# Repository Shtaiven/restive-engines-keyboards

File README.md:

# restive.engines Keyboards

## Introduction

This repository contains design and manufacturing files created by Steven Eisinger (@Shtaiven a.k.a. restive.engines). Everything you need to manufacture one of my keyboards can be found here, including pcbs, cases, and certain keycaps.

For keyboard firmware, please refer to my [ZMK config repo](https://github.com/Shtaiven/restive-engines-zmk-config).

## Keyboards

### fairyboard

[Build guide](docs/fairyboard.md)

Designed in 2024. Made to address shortcomings and enhance ergonomics of the shockboard. Ergonomic column staggered keyboard extendable with custom modules using terminal blocks or headers. 14 degree rotation on each half. Compatible with MX, Choc v1, and Choc v2 switches.

### shockboard

[Build guide](docs/shockboard.md)

Designed in 2023. My first custom keyboard. Ergonomic column staggered keyboard with a number row, compatible with 1.25u thumb keys. 10 degree rotation on each half. Compatible with MX and Choc v1 switches.

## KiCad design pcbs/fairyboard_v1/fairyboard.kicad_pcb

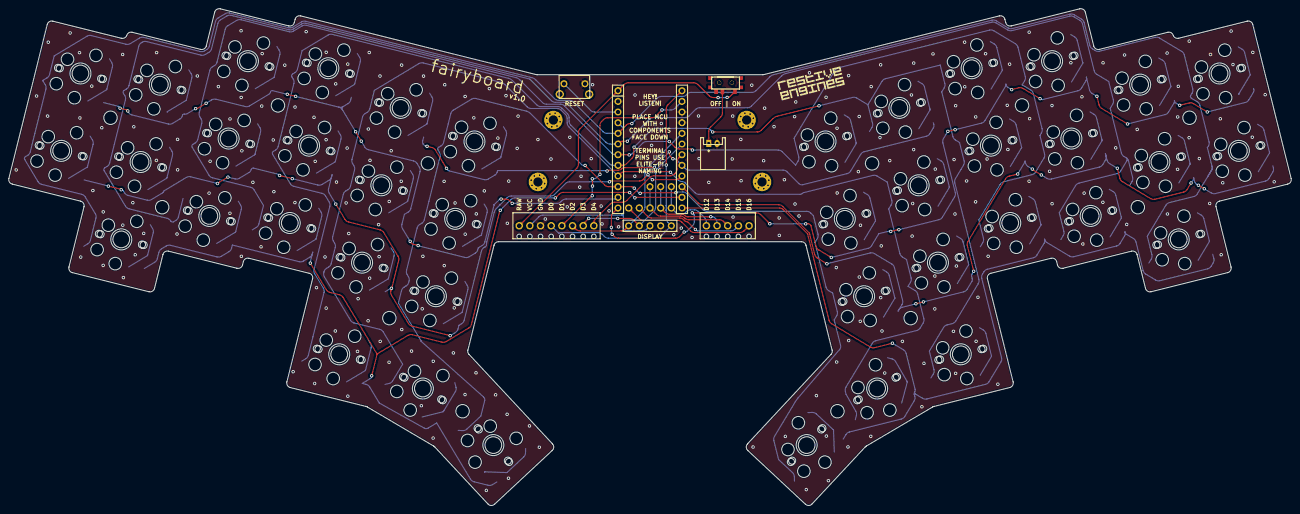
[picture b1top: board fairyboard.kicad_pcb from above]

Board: 2 copper layers, 305.6 x 118.3 mm, 142 parts (0 on the bottom side), 60 nets.

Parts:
D1, D2, D3, D4, D5, D6, D7, D8, D9, D10, D11, D12, D13, D14, D15, D16, D17, D18, D19, D20, D21, D22, D23, D24, D25, D26, D27, D28, D29, D30, D31, D32, D33, D34, D35, D36, D37, D38, D39, D40: SmtDiode
DISP1: display_nice_view
JST1: JST_PH_S2B-PH-K_02x2.00mm_Angled
RST1: reset_switch_tht_side
S1, S2, S3, S4, S5, S6, S7, S8, S9, S10, S11, S12, S13, S14, S15, S16, S17, S18, S19, S20, S21, S22, S23, S24, S25, S26, S27, S28, S29, S30, S31, S32, S33, S34, S35, S36, S37, S38, S39, S40: MX
S41, S42, S43, S44, S45, S46, S47, S48, S49, S50, S51, S52, S53, S54, S55, S56, S57, S58, S59, S60, S61, S62, S63, S64, S65, S66, S67, S68, S69, S70, S71, S72, S73, S74, S75, S76, S77, S78, S79, S80: PG1350
T1: SPDT_C128955
TERMINAL1: terminal_block_8
TERMINAL2: terminal_block_5
_2, _3, _4, _5, _6, _7, _8, _9, _10, _11, _12, _13: SpacerHole_3.2mm_M2_Pad_Via
_14, _15, _16, _17: MountingHole_2.2mm_M2_Pad_Via

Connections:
B+: JST1.1, T1.2
COL1: S1.1, S2.1, S3.1, S21.1, S22.1, S23.1, S41.2, S42.2, S43.2, S61.2, S62.2, S63.2
COL2: S4.1, S5.1, S6.1, S24.1, S25.1, S26.1, S44.2, S45.2, S46.2, S64.2, S65.2, S66.2
COL3: S7.1, S8.1, S9.1, S27.1, S28.1, S29.1, S37.1, S47.2, S48.2, S49.2, S67.2, S68.2, S69.2, S77.2
COL4: S10.1, S11.1, S18.1, S30.1, S31.1, S34.1, S38.1, S50.2, S51.2, S58.2, S70.2, S71.2, S74.2, S78.2
COL5: S12.1, S13.1, S14.1, S19.1, S32.1, S33.1, S39.1, S52.2, S53.2, S54.2, S59.2, S72.2, S73.2, S79.2
COL6: S15.1, S16.1, S17.1, S20.1, S35.1, S36.1, S40.1, S55.2, S56.2, S57.2, S60.2, S75.2, S76.2, S80.2
D0: DISP1.5, TERMINAL1.4
D2: DISP1.1, TERMINAL1.6
D3: DISP1.2, TERMINAL1.7
GND: DISP1.4, JST1.2, RST1.1, TERMINAL1.3
RAW: T1.1, TERMINAL1.1
ROW1: D14.1, D17.1, D34.1, D37.1
ROW2: D2.1, D5.1, D8.1, D11.1, D13.1, D16.1
ROW3: D1.1, D4.1, D7.1, D10.1, D12.1, D15.1
ROW4: D3.1, D6.1, D9.1, D18.1, D19.1, D20.1
ROW5: D22.1, D25.1, D28.1, D31.1, D33.1, D36.1
ROW6: D21.1, D24.1, D27.1, D30.1, D32.1, D35.1
ROW7: D23.1, D26.1, D29.1, D38.1, D39.1, D40.1
VCC: DISP1.3, TERMINAL1.2
index_bottom: D12.2, S12.2, S52.1
index_home: D13.2, S13.2, S53.1
index_top: D14.2, S14.2, S54.1
inner_bottom: D15.2, S15.2, S55.1
inner_home: D16.2, S16.2, S56.1
inner_thumb: D20.2, S20.2, S60.1
inner_top: D17.2, S17.2, S57.1
middle_bottom: D9.2, S9.2, S49.1
middle_home: D10.2, S10.2, S50.1
middle_thumb: D19.2, S19.2, S59.1
middle_top: D11.2, S11.2, S51.1
mirror_index_bottom: D32.2, S32.2, S72.1
mirror_index_home: D33.2, S33.2, S73.1
mirror_index_top: D34.2, S34.2, S74.1
mirror_inner_bottom: D35.2, S35.2, S75.1
mirror_inner_home: D36.2, S36.2, S76.1
mirror_inner_thumb: D40.2, S40.2, S80.1
mirror_inner_top: D37.2, S37.2, S77.1
mirror_middle_bottom: D29.2, S29.2, S69.1
mirror_middle_home: D30.2, S30.2, S70.1
mirror_middle_thumb: D39.2, S39.2, S79.1
mirror_middle_top: D31.2, S31.2, S71.1
mirror_outer_home: D21.2, S21.2, S61.1
mirror_outer_thumb: D38.2, S38.2, S78.1
mirror_outer_top: D22.2, S22.2, S62.1
mirror_pinky_bottom: D23.2, S23.2, S63.1
mirror_pinky_home: D24.2, S24.2, S64.1
mirror_pinky_top: D25.2, S25.2, S65.1
mirror_ring_bottom: D26.2, S26.2, S66.1
mirror_ring_home: D27.2, S27.2, S67.1
mirror_ring_top: D28.2, S28.2, S68.1
outer_home: D1.2, S1.2, S41.1
outer_thumb: D18.2, S18.2, S58.1
outer_top: D2.2, S2.2, S42.1
pinky_bottom: D3.2, S3.2, S43.1
pinky_home: D4.2, S4.2, S44.1
pinky_top: D5.2, S5.2, S45.1
ring_bottom: D6.2, S6.2, S46.1
ring_home: D7.2, S7.2, S47.1
ring_top: D8.2, S8.2, S48.1

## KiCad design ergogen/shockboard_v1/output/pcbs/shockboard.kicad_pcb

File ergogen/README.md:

# Ergogen configuration files

This folder contains the input and ouputs of ergogen to generate the shockboard layout.

## Note on compatibility

Ergogen v4.0.0 introduced breaking changes to configuration. Config files will only work with ergogen >= v4.0.0.

## Generating layouts

Due to the use of custom footprints, [ergogen](ergogen.xyz) must be installed locally and the online versions can't be used.
Before running anything below, ensure [npm](https://docs.npmjs.com/downloading-and-installing-node-js-and-npm) is installed on your system.

```shell
npm install -g ergogen@4
```

Output folders and are generated by calling ergogen in one of the revision folders e.g.

```shell
cd ergogen/shockboard_v1
ergogen .
```

The unrouted pcbs can then be found in the `output/pcbs` folder.

## Generating STLs

The ergogen config generates some cases in jscad format. Before converting these to STL files [jscad/cli](https://github.com/jscad/OpenJSCAD.org) must be installed.

```shell
npm install -g @jscad/cli
```

To generate the STLs, run the following from one of the revision folders (e.g. `shockboard_v1`)

```shell
for i in output/cases/*.jscad; do npx @jscad/cli@1 "$i" -of stla; done
```

The STLs can then be found in the `outpud/cases` folder.

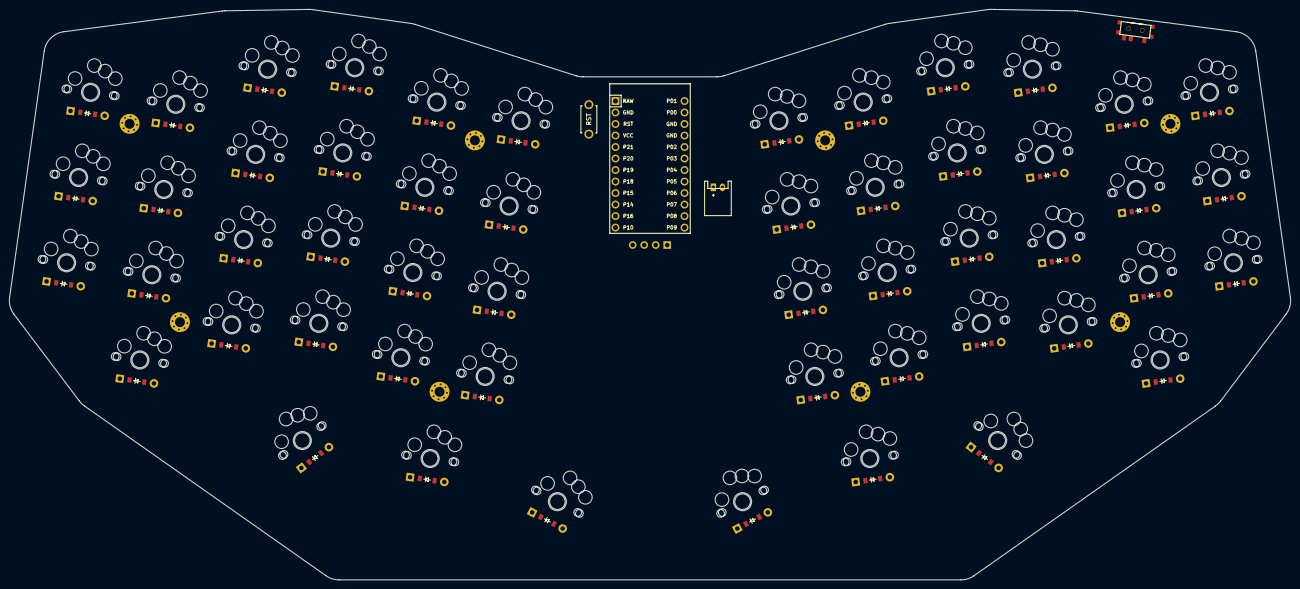
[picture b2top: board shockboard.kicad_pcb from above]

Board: 2 copper layers, 282.9 x 126.0 mm, 169 parts (0 on the bottom side), 75 nets, no tracks yet.

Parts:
D1, D2, D3, D4, D5, D6, D7, D8, D9, D10, D11, D12, D13, D14, D15, D16, D17, D18, D19, D20, D21, D22, D23, D24, D25, D26, D27, D28, D29, D30, D31, D32, D33, D34, D35, D36, D37, D38, D39, D40, D41, D42, D43, D44, D45, D46, D47, D48, D49, D50, D51, D52: ComboDiode
JST1: JST_PH_S2B-PH-K_02x2.00mm_Angled
MCU1: ProMicro
OLED1: OLED; OLED_headers
RST1: reset_switch_tht_top
S1, S2, S3, S4, S5, S6, S7, S8, S9, S10, S11, S12, S13, S14, S15, S16, S17, S18, S19, S20, S21, S22, S23, S24, S25, S26, S27, S28, S29, S30, S31, S32, S33, S34, S35, S36, S37, S38, S39, S40, S41, S42, S43, S44, S45, S46, S47, S48, S49, S50, S51, S52: MX
S53, S54, S55, S56, S57, S58, S59, S60, S61, S62, S63, S64, S65, S66, S67, S68, S69, S70, S71, S72, S73, S74, S75, S76, S77, S78, S79, S80, S81, S82, S83, S84, S85, S86, S87, S88, S89, S90, S91, S92, S93, S94, S95, S96, S97, S98, S99, S100, S101, S102, S103, S104: PG1350
T1: SPDT_C128955
_1, _2, _3, _4, _5, _6, _7, _8: MountingHole_2.2mm_M2_Pad_Via

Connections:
B+: JST1.1, T1.2
GND: JST1.2, MCU1.2, MCU1.15, MCU1.16, OLED1.1, RST1.2
P0: D27.1, D31.1, D35.1, D39.1, D43.1, D47.1, MCU1.14
P1: D30.1, D34.1, D38.1, D42.1, D46.1, MCU1.13
P2: MCU1.17, OLED1.4
P3: MCU1.18, OLED1.3
P4: D28.1, D32.1, D36.1, D40.1, D44.1, D48.1, MCU1.19
P5: D29.1, D33.1, D37.1, D41.1, D45.1, D49.1, MCU1.20
P6: D50.1, D51.1, D52.1, MCU1.21
P7: MCU1.22, S12.1, S13.1, S14.1, S15.1, S24.1, S38.1, S39.1, S40.1, S41.1, S50.1, S64.1, S65.1, S66.1, S67.1, S76.1, S90.1, S91.1, S92.1, S93.1, S102.1
P8: MCU1.23, S16.1, S17.1, S18.1, S19.1, S25.1, S42.1, S43.1, S44.1, S45.1, S51.1, S68.1, S69.1, S70.1, S71.1, S77.1, S94.1, S95.1, S96.1, S97.1, S103.1
P9: MCU1.24, S20.1, S21.1, S22.1, S23.1, S26.1, S46.1, S47.1, S48.1, S49.1, S52.1, S72.1, S73.1, S74.1, S75.1, S78.1, S98.1, S99.1, S100.1, S101.1, S104.1
P10: MCU1.12, S8.1, S9.1, S10.1, S11.1, S34.1, S35.1, S36.1, S37.1, S60.1, S61.1, S62.1, S63.1, S86.1, S87.1, S88.1, S89.1
P14: MCU1.10, S1.1, S2.1, S3.1, S27.1, S28.1, S29.1, S53.1, S54.1, S55.1, S79.1, S80.1, S81.1
P15: D24.1, D25.1, D26.1, MCU1.9
P16: MCU1.11, S4.1, S5.1, S6.1, S7.1, S30.1, S31.1, S32.1, S33.1, S56.1, S57.1, S58.1, S59.1, S82.1, S83.1, S84.1, S85.1
P18: D3.1, D7.1, D11.1, D15.1, D19.1, D23.1, MCU1.8
P19: D2.1, D6.1, D10.1, D14.1, D18.1, D22.1, MCU1.7
P20: D1.1, D5.1, D9.1, D13.1, D17.1, D21.1, MCU1.6
P21: D4.1, D8.1, D12.1, D16.1, D20.1, MCU1.5
RAW: MCU1.1, T1.1
RST: MCU1.3, RST1.1
VCC: MCU1.4, OLED1.2
index_bottom: D16.2, S16.2, S68.2
index_home: D17.2, S17.2, S69.2
index_num: D19.2, S19.2, S71.2
index_top: D18.2, S18.2, S70.2
inner_bottom: D20.2, S20.2, S72.2
inner_home: D21.2, S21.2, S73.2
inner_num: D23.2, S23.2, S75.2
inner_thumb: D26.2, S26.2, S78.2
inner_top: D22.2, S22.2, S74.2
middle_bottom: D12.2, S12.2, S64.2
middle_home: D13.2, S13.2, S65.2
middle_num: D15.2, S15.2, S67.2
middle_thumb: D25.2, S25.2, S77.2
middle_top: D14.2, S14.2, S66.2
mirror_index_bottom: D42.2, S42.2, S94.2
mirror_index_home: D43.2, S43.2, S95.2
mirror_index_num: D45.2, S45.2, S97.2
mirror_index_top: D44.2, S44.2, S96.2
mirror_inner_bottom: D46.2, S46.2, S98.2
mirror_inner_home: D47.2, S47.2, S99.2
mirror_inner_num: D49.2, S49.2, S101.2
mirror_inner_thumb: D52.2, S52.2, S104.2
mirror_inner_top: D48.2, S48.2, S100.2
mirror_middle_bottom: D38.2, S38.2, S90.2
mirror_middle_home: D39.2, S39.2, S91.2
mirror_middle_num: D41.2, S41.2, S93.2
mirror_middle_thumb: D51.2, S51.2, S103.2
mirror_middle_top: D40.2, S40.2, S92.2
mirror_outer_home: D27.2, S27.2, S79.2
mirror_outer_num: D29.2, S29.2, S81.2
mirror_outer_thumb: D50.2, S50.2, S102.2
mirror_outer_top: D28.2, S28.2, S80.2
mirror_pinky_bottom: D30.2, S30.2, S82.2
mirror_pinky_home: D31.2, S31.2, S83.2
mirror_pinky_num: D33.2, S33.2, S85.2
mirror_pinky_top: D32.2, S32.2, S84.2
mirror_ring_bottom: D34.2, S34.2, S86.2
mirror_ring_home: D35.2, S35.2, S87.2
mirror_ring_num: D37.2, S37.2, S89.2
mirror_ring_top: D36.2, S36.2, S88.2
outer_home: D1.2, S1.2, S53.2
outer_num: D3.2, S3.2, S55.2
outer_thumb: D24.2, S24.2, S76.2
outer_top: D2.2, S2.2, S54.2
pinky_bottom: D4.2, S4.2, S56.2
pinky_home: D5.2, S5.2, S57.2
pinky_num: D7.2, S7.2, S59.2
pinky_top: D6.2, S6.2, S58.2
ring_bottom: D8.2, S8.2, S60.2
ring_home: D9.2, S9.2, S61.2
ring_num: D11.2, S11.2, S63.2
ring_top: D10.2, S10.2, S62.2

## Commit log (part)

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2021-09-28 Organized for kicad
2021-10-01 created the keyboard matrix in the schematic
2021-11-23 Changed directory structure, made second half of the keyboard, added nicenano
2022-06-14 Added new kicad file format and preliminary ergogen layout
2022-06-27 Modified ergogen thumb measurements
2022-08-02 Somewhat finalized the layout for the first version in ergogen
2022-08-26 misc: add rotation and change thumbs slightly
2022-08-27 Update gitignore and ergogen spacing and rotation
2022-08-31 misc: attempt plate and anchors refed on home keys
2022-09-01 misc: added cutout and plate outline prototype
2022-09-01 misc: organize using some comments
2022-09-01 misc: playing around with plate shape
2022-09-05 Made the outline more rectangular
2022-09-13 misc: some plate outline experiments
2022-09-15 misc: added variables to ergogen
2022-09-26 misc: add corner radii to units and some renaming
2022-09-28 misc: add a forehead to the bend plates
2022-10-13 Added lots of files used for the 3d model
2022-10-18 feat: started adjusting v0.2 layout. Reorganized some folders
2022-10-18 misc: unit U->u
2022-10-18 feat: removed a key and tuned v0.2
2022-10-18 feat: added dxf files for v0.2
2022-10-20 feat: finish plate v0.2
2022-10-20 feat: assembled shockboard v0.2
2022-10-20 feat: added full assembly and created a riser
2022-10-21 Add screw holes and text
2022-10-21 Added svg files for fab and changed to M3 screws
2022-10-21 Added panels for laser cutting
2022-11-09 fix: added shockboard_v0.3 with TODOS
2022-11-11 misc: added more units for easy adjustment
2022-12-11 feat: add an extra key row and some minor adjustments
2023-07-15 fix: update v0.2 for ergogen v4
2023-07-15 fix: update v0.3 for ergogen v4
2023-07-15 misc: formatting
2023-07-16 feat: add v0.4.0, update versioning
2023-07-16 feat: better parametrization
2023-07-16 feat: tuning v0.4.0
2023-07-16 feat: ergogen explanation and store ergogen output
2023-07-16 feat: added simple fab files for shockboard v0.4
2023-08-18 wip: pcb with ergogen
2023-09-12 feat: adjusted mcu shift
2024-02-09 feat: corrected nets for rows and columns
2024-02-09 feat: added choc hotswap and battery connector
2024-03-10 wip: outline redesign
2024-03-10 feat: flattened out pcb bottom
2024-03-17 feat: slightly flatter bottom and slightly tighter choc plates
2024-04-06 feat: added reset switch and oled
2024-04-06 feat: added battery switch
2024-04-08 wip: mounting holes
2024-04-08 feat: added mounting holes
2024-04-10 feat: move battery connector down
2024-04-13 feat: change and veryify pins
2024-04-13 feat: use config.yaml as ergogen config name
2024-04-13 feat: replace ecad with the current ergogen output v0.4.0
2024-04-13 wip: routing
2024-04-14 wip: routing and fill, missing ground plane vias and silkscreen
2024-04-14 docs: update readme
2024-04-14 feat: clean up a few traces
2024-04-16 feat: complete board with fab, no silkscreen yet
2024-04-17 feat: v1 fab files
2024-04-19 feat: added flatfootfox style minimal case
2024-04-20 feat: cleaned up minimal case and config a bit
2024-04-20 feat: added several different case variations
2024-05-09 feat: make plates and accomodate heatset inserts
2024-05-09 feat: clean up repository and ergogen readme
2024-05-09 feat: rename fabrication zip and add info about manufacturing and firmware
2024-05-09 misc: prep for openscad case
2024-05-09 wip: top and bottom hipro case in openscad (missing some holes)
2024-05-11 added a case assembly
2024-05-11 feat: added screws, standoffs, and inserts and corrected assembly
2024-05-11 feat: add hole in top case for promicro and screen
2024-05-11 feat: usbc hole
2024-05-11 feat: battery switch cutout
2024-05-11 feat: shockboard v1 case stls
2024-05-11 feat: print files
2024-05-11 misc: regular gcode files for printer compatibility
2024-05-12 fix: add 1mm clearance to case hipro bottom mx
2024-05-12 feat: enable ironing on top case
2024-05-12 misc: remove previous bottom case gcode
2024-05-14 feat: adjusted hipro mx case for better tolerances and correct heatset insert sizes. Added lowpro mx case.
2024-05-15 feat: generate models and remove old fab files
2024-05-18 feat: space for cable around board edge for nice view
2024-05-20 feat: test config for printing and overhang on bottom cases
2024-05-20 feat: remove unneeded parts and added split hipro case stls
2024-05-24 misc: update todos for v2
2024-05-26 misc: update scad files for better support under pcb and wider thumb keywell
2024-05-28 feat: fixes for thumb keywell and added a pcb spacer
2024-06-02 feat: added internal support structure to cases and added pcb spacer
2024-06-02 feat: hipro print files and config
2024-06-15 feat: added assembly instructions to the readme
2024-06-15 docs: add image of shockboard
2024-06-15 docs: minor readme edit
2024-06-21 feat: move footprints dir to be common between boards and generate first fairyboard
2024-06-21 feat: modified rotation, thumb cluster, and split distance
2024-06-22 feat: added nice_view
2024-06-22 wip: invert choc hotswap and move diodes
2024-06-22 feat: added logo
2024-06-23 feat: change logo to black text on white background
2024-06-25 feat: update keywell_mx
2024-07-25 feat: remove top row and modify thumb cluster
2024-08-05 feat: prototyping shape of fairyboard and added key position adjustments to ergogen
2024-08-19 feat: adjust stagger on outer and inner column
2024-08-19 feat: complete fairyboard shape
2024-08-20 feat: remove a large blank space near board bottom
2024-08-20 feat: reverse column and row net of inverted chocs
2024-08-23 feat: added poetry config for build123d and import board
2024-08-24 feat: add ruff and pyright to pyproject and apply ruff format
2024-08-24 feat: remove unneeded files and dirs
2024-09-18 feat: vik connector
2024-09-24 feat: added reset switch side
2024-09-24 feat: move components onto the board
2024-09-25 feat: create spacerhole and move them to appropriate positions
2024-09-25 feat: move diodes
2024-09-26 fix: VIK OUT instead of VIK IN
2024-09-26 feat: add vik throughhole
2024-09-28 feat: mounting for a screen
2024-09-28 feat: plate mounting holes
2024-09-28 fix: adjust bottom mounting holes
2024-09-29 feat: increase fillet size to prevent DRC error
2024-10-01 feat: added nice_nano and elite_c compatible footprint
2024-10-02 feat: correct flipped silkscreen
2024-10-05 feat: terminal block
2024-10-05 feat: move mounting hole for screen up and make silkscreen visible for terminal_block
2024-10-06 misc: move labels of terminal block a bit up
2024-10-06 misc: correct nets for all rows and columns
2024-10-06 feat: wire to mcu
2024-10-06 misc: adjust spacer hole clearance
2024-10-07 misc: correct pin order on mcu
2024-10-07 misc: pin holes for terminal block
2024-10-07 feat: simple cases (missing cutouts)
2024-10-07 feat: function cases and testing plate
2024-10-07 feat: test case halves
2024-10-09 feat: added choc v2 compatibility
2024-10-09 feat: minor adjustments to component placement and switch D5 for D1 as default cs pin
2024-10-10 misc: move jst connector up and fix - character
2024-10-10 misc: remove bpos and bneg pins
2024-10-10 feat: added terminal block for extra pins and rearranged terminal block pins
2024-10-10 feat: save and move pcb to pcbs folder
2024-10-13 feat: resave pcb
2024-10-13 feat: adjustments to top of pcb and silkscreen
2024-10-13 feat: route middle of pcb
2024-10-14 feat: first routing pass
2024-10-14 feat: fully connected pcb
2024-10-15 feat: fairyboard branding
2024-10-15 feat: restive.engines branding
2024-10-18 fix: border outline
2024-10-19 feat: add silkscreen and source images
2024-10-19 feat: sparkles
2024-10-19 misc: remove halftone dots where possible to reduce pcb size
2024-10-20 feat: added fabrication files
2024-10-20 feat: added manufacturing zip and keycaps
2024-10-20 feat: rearrange docs and added preliminary fairyboard bom
2024-10-20 feat: remove version in readme and add image
2024-10-20 misc: cleanup unused pyproject and add step file
2024-10-20 feat: some documentation
2024-10-22 feat: cad for simple cases
2024-10-22 feat: added simple case stls
2024-10-23 feat: added some construction outlines for future cad work
2024-10-24 feat: consolidate top case/plate cad and create top cases
2024-10-24 feat: adjustments to pcb outline translation
2024-11-02 feat: fairyboard bottom simple case
2024-11-02 feat: printing files for top case
2024-11-02 feat: added choc v2 top case print files
2024-11-03 feat: complete bottom case and top case refactor
2024-11-04 feat: fillet top case and refine top and bottom case
2024-11-04 feat: create an assembly
2024-11-04 feat: simple center window generation
2024-11-05 feat: added fillet utils and use on center window
2024-11-08 feat: inner window mods and todos
2024-11-09 feat: some cutouts on top case and refined bottom case
2024-11-10 feat: export all cases and plates
2024-11-12 feat: added a low profile case
2024-11-12 feat: added lowpro 3mf
2024-11-16 feat: added SCUF feet detents
2024-11-21 feat: scuf cutouts and center window cutout
2024-11-21 feat: refine center window
2024-11-23 feat: create flat center window and a dxf for a plate
2024-11-23 misc: simple_case to slim_case
2024-11-24 feat: modify the center window to be lower profile and generate several versions (case and plate)
2024-12-01 feat: cleanup and fix SCUF bumpons
2025-03-21 misc: add split bottom case 3mf for printing
2025-03-21 feat: added wider holes for bottom case when printing resin
2025-03-21 feat: correct inserts for resin
2025-04-04 fix: update repo link
2026-05-03 feat: corner rounding and fillet options for top case
2026-05-03 feat: resin compatibility on bottom case inserts
2026-05-03 fix: center window doesn't start with number
2026-05-03 feat: cutouts for power, reset, terminal on bottom case with wall
2026-05-03 feat: stls for bottom and top of slim_case_with_walls
2026-05-04 feat: printable bottom case for slim case with wall
2026-05-04 feat: center window remove roundedness and fix top case for slim with walls
2026-05-09 feat: refined center window and bottom case for wall
2026-05-09 feat: 3mf files for new center window and bottom hase for slim lp with walls
2026-05-12 misc: add cad todos
2026-05-18 feat: some refinement in the chamfer around the window cutout
2026-05-18 feat: export new chamfered window and bottom
2026-06-01 feat: new centered window for slim case with walls
2026-06-02 feat: pcb-place spacer generation and window bump top chamfer parameterization
